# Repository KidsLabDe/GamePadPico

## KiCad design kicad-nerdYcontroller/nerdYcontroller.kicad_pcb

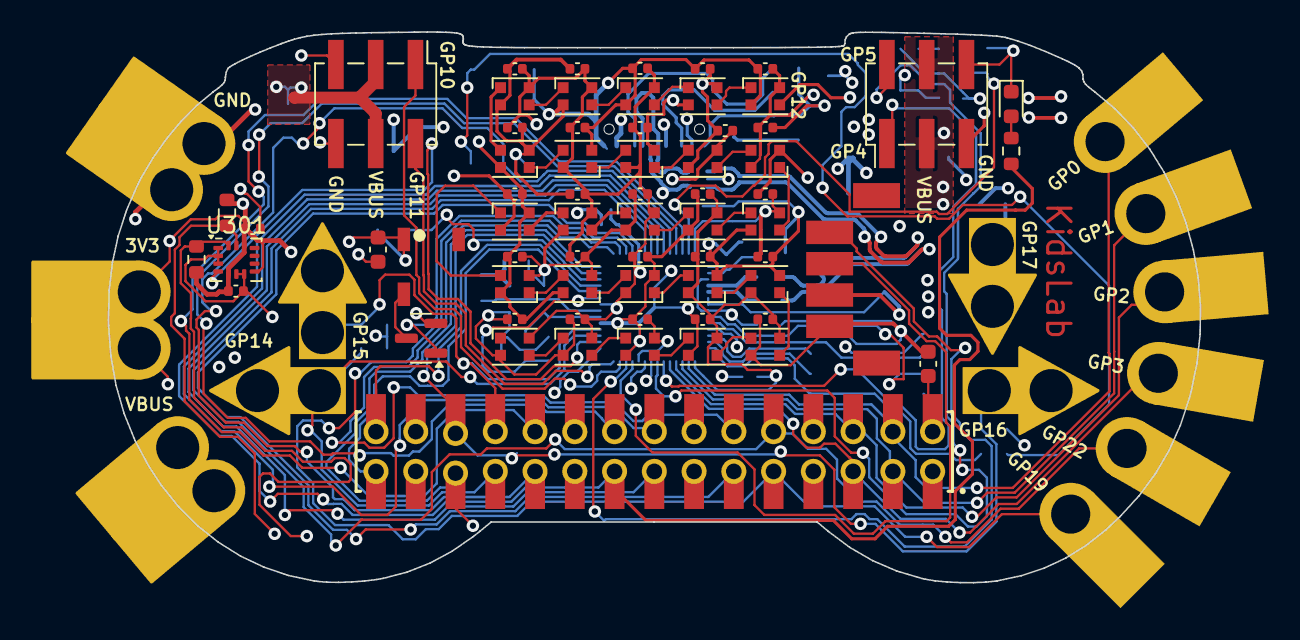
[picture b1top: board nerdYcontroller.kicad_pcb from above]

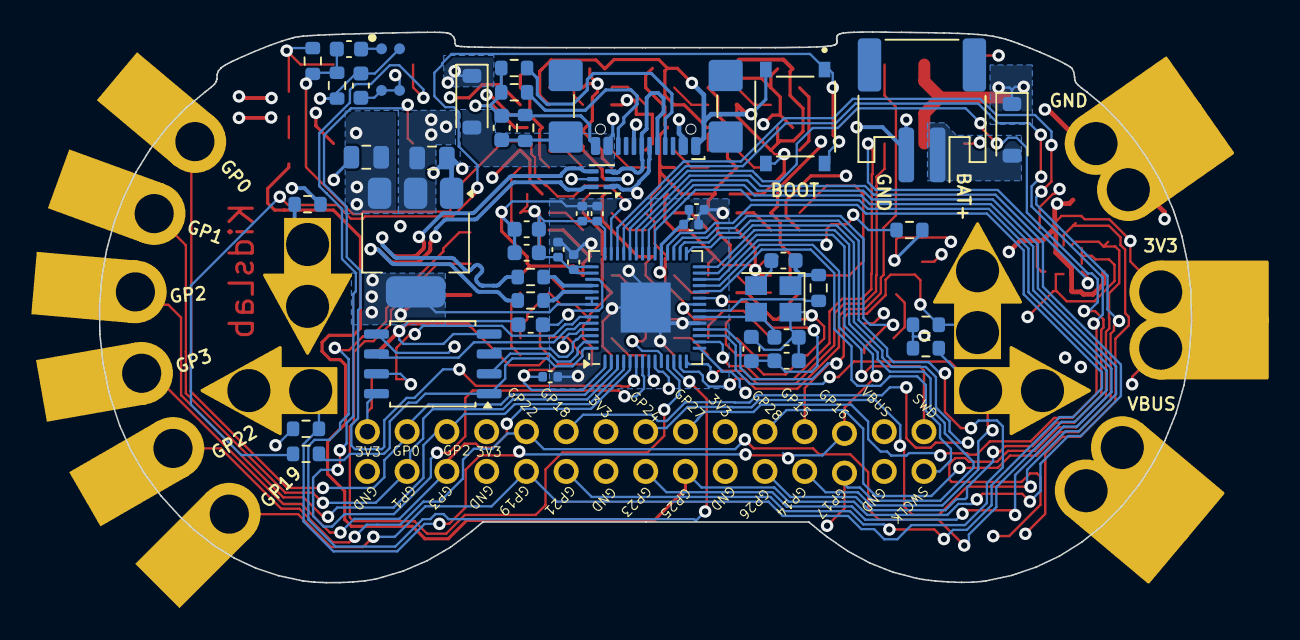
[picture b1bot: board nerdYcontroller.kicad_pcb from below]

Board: 4 copper layers, 69.8 x 35.2 mm, 123 parts (44 on the bottom side), 85 nets.

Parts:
3V3: kroko_doubleedge; DoubleEdge
A301, A302, A303, A304: arrow; Kroko_Arrow
BZ301: Buzzer-FUET-5020; FUET-5020
C101, C113, C114, C304: 100nF; C_0603_1608Metric
C102, C103: 22pF; C_0603_1608Metric
C104, C105, C106, C107, C108, C109, C110, C301, C302, C401, C402, C403, C404, C405, C406, C407, C408, C409, C410, C411, C412, C413, C414, C415, C416, C417, C418, C419, C420, C421, C422, C423, C424, C425: 100nF; C_0402_1005Metric
C111: 10uF; C_0603_1608Metric
C112, C115, C303, C305: 1uF; C_0603_1608Metric
C201, C202: 10uF; C_0805_2012Metric
C203: 1nF; C_0603_1608Metric
D201, D203: B5817W; D_SOD-123
D202: PRTR5V0U2F; WSON-6_1.5x1.5mm_P0.5mm
D301: KT-0603R; LED_0603_1608Metric
D401, D402, D403, D404, D405, D406, D407, D408, D409, D410, D411, D412, D413, D414, D415, D416, D417, D418, D419, D420, D421, D422, D423, D424, D425: WS2812B-2020; LED_WS2812B-2020_PLCC4_2.0x2.0mm
GND301: kroko_doubleedge; DoubleEdge
GP0, GP1, GP2, GP3, GP19, GP22: kroko_edge; Edgeconnector
J201: S2B-PH-SM4-TB; JST_PH_S2B-PH-SM4-TB_1x02-1MP_P2.00mm_Horizontal
J301, J302: Conn_02x03_Odd_Even; PinHeader_2x03_P2.54mm_Vertical_SMD
J303: ZX-HY2.0-4PLT
J304: HLE-115-02-F-DV; SAMTEC_HLE-115-02-F-DV
P201: USB_C_Plug_USB2.0; USB_C_Receptacle_GCT_USB4110
Q301: DDTC113ZCA; SOT-23
R101, R102, R105, R307: 1k; R_0603_1608Metric
R103, R104: 27R; R_0603_1608Metric
R201, R202: 5k1; R_0603_1608Metric
R203: 100; R_0603_1608Metric
R301, R302: 10k; R_0603_1608Metric
R303, R304, R305, R306: 1M; R_0603_1608Metric
R308: 33k; R_0603_1608Metric
R309: 330R; R_0603_1608Metric
S101: TS-1187A-B-A-B; SW_TS-1187A-B-A-B
U101: RP2040; QFN-56-1EP_7x7mm_P0.4mm_EP3.2x3.2mm
U102: W25Q128JVS; SOIC-8_5.23x5.23mm_P1.27mm
U201: AMS1117-3.3; SOT-223-3_TabPin2
U301: LSM6DS3TR-C; LGA-14_3x2.5mm_P0.5mm_LayoutBorder3x4y
U302: LMA3722T421-OA5
VBUS301: kroko_doubleedge; DoubleEdge
Y101: Crystal_GND24; Crystal_SMD_3225-4Pin_3.2x2.5mm
outline: Gamecontroller Outline

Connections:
+1V1: C113.1, C114.1, C115.1, U101.23 (DVDD), U101.45 (VREG_VOUT), U101.50 (DVDD)
+3V3: 3V3.1, BZ301.1 (+), C101.1, C104.2, C105.2, C106.2, C107.2, C108.2, C109.2, C110.2, C111.1, C112.1, C202.1, C301.2, C302.2, C304.1, C305.1, C401.1, C402.1, C403.1, C404.1, C405.1, C406.1, C407.1, C408.1, C409.1, C410.1, C411.1, C412.1, C413.1, C414.1, C415.1, C416.1, C417.1, C418.1, C419.1, C420.1, C421.1, C422.1, C423.1, C424.1, C425.1, D401.4 (VDD), D402.4 (VDD), D403.4 (VDD), D404.4 (VDD), D405.4 (VDD), D406.4 (VDD), D407.4 (VDD), D408.4 (VDD), D409.4 (VDD), D410.4 (VDD), D411.4 (VDD), D412.4 (VDD), D413.4 (VDD), D414.4 (VDD), D415.4 (VDD), D416.4 (VDD), D417.4 (VDD), D418.4 (VDD), D419.4 (VDD), D420.4 (VDD), D421.4 (VDD), D422.4 (VDD), D423.4 (VDD), D424.4 (VDD), D425.4 (VDD), J303.3, J304.02, J304.08, J304.14, J304.20, R102.2, R301.1, R302.1, R308.1, U101.1 (IOVDD), U101.10 (IOVDD), U101.22 (IOVDD), U101.33 (IOVDD), U101.42 (IOVDD), U101.43 (ADC_AVDD), U101.44 (VREG_IN), U101.48 (USB_VDD), U101.49 (IOVDD), U102.8 (VCC), U201.2 (VO), U301.5 (VDDIO), U301.8 (VDD), U301.12 (CS), U302.2 (VDD)
/FLASH_CS: R101.2, U101.56 (QSPI_SS), U102.1 (~CS)
/FLASH_SCLK: U101.52 (QSPI_SCLK), U102.6 (CLK)
/FLASH_SD0: U101.53 (QSPI_SD0), U102.5 (DI(IO0))
/FLASH_SD1: U101.55 (QSPI_SD1), U102.2 (DO(IO1))
/FLASH_SD2: U101.54 (QSPI_SD2), U102.3 (IO2)
/FLASH_SD3: U101.51 (QSPI_SD3), U102.7 (IO3)
/N_USBBOOT: R101.1, S101.A, S101.B
/Peripherals/GP0: GP0.1, J304.04, U101.2 (GPIO0)
/Peripherals/GP1: GP1.1, J304.03, U101.3 (GPIO1)
/Peripherals/GP2: GP2.1, J304.06, U101.4 (GPIO2)
/Peripherals/GP3: GP3.1, J304.05, U101.5 (GPIO3)
/Peripherals/GP4/SERVO_2: J302.1, U101.6 (GPIO4)
/Peripherals/GP5/SERVO_3: J302.2, U101.7 (GPIO5)
/Peripherals/GP6/IMU_SDA: R301.2, U101.8 (GPIO6), U301.14 (SDA)
/Peripherals/GP7/IMU_SCL: R302.2, U101.9 (GPIO7), U301.13 (SCL)
/Peripherals/GP8/Grove_D1: J303.2, U101.11 (GPIO8)
/Peripherals/GP9/Grove_D0: J303.1, U101.12 (GPIO9)
/Peripherals/GP10/SERVO_0: J301.1, U101.13 (GPIO10)
/Peripherals/GP11/SERVO_1: J301.2, U101.14 (GPIO11)
/Peripherals/GP12/NEOPIXEL: D401.3 (DIN), U101.15 (GPIO12)
/Peripherals/GP13/INTR: U101.16 (GPIO13), U301.4 (INT1)
/Peripherals/GP14/ArrowLeft: A301.1, J304.23, R303.1, U101.17 (GPIO14)
/Peripherals/GP15/ArrowUp: A302.1, J304.24, R304.1, U101.18 (GPIO15)
/Peripherals/GP16/ArrowRight: A303.1, J304.26, R305.1, U101.27 (GPIO16)
/Peripherals/GP17/ArrowDown: A304.1, J304.25, R306.1, U101.28 (GPIO17)
/Peripherals/GP18: J304.12, U101.29 (GPIO18)
/Peripherals/GP19: GP19.1, J304.09, U101.30 (GPIO19)
/Peripherals/GP20/Buzzer: Q301.1 (B), U101.31 (GPIO20)
/Peripherals/GP21: J304.11, U101.32 (GPIO21)
/Peripherals/GP22: GP22.1, J304.10, U101.34 (GPIO22)
/Peripherals/GP23: J304.15, U101.35 (GPIO23)
/Peripherals/GP24: J304.16, U101.36 (GPIO24)
/Peripherals/GP25/LED: J304.17, R309.1, U101.37 (GPIO25)
/Peripherals/GP26: J304.21, U101.38 (GPIO26_ADC0)
/Peripherals/GP27: J304.18, U101.39 (GPIO27_ADC1)
/Peripherals/GP28: J304.22, U101.40 (GPIO28_ADC2)
/Peripherals/GP29/MIC_OUT: C303.2, R307.1, R308.2, U101.41 (GPIO29_ADC3)
/SWCLK: J304.29, U101.24 (SWCLK)
/SWD: J304.30, U101.25 (SWD)
/VBUS: C201.1, D201.1 (K), D203.1 (K), J301.3, J301.4, J302.3, J302.4, J304.28, U201.3 (VI), VBUS301.1
/d+: R103.2, U101.47 (USB_DP)
/d-: R104.2, U101.46 (USB_DM)
/power-and-usb/USBC-D+: D202.1 (IO1), P201.A6 (D+), P201.B6 (D+)
/power-and-usb/USBC-D-: D202.3 (IO2), P201.A7 (D-), P201.B7 (D-)
/power-and-usb/usb_vcc: D201.2 (A), D202.5 (VCC), P201.A4 (VBUS), P201.A9 (VBUS), P201.B4 (VBUS), P201.B9 (VBUS)
/usb_d+: D202.6 (IO1), R103.1
/usb_d-: D202.4 (IO2), R104.1
GND: C101.2, C102.2, C103.2, C104.1, C105.1, C106.1, C107.1, C108.1, C109.1, C110.1, C111.2, C112.2, C113.2, C114.2, C115.2, C201.2, C202.2, C203.2, C301.1, C302.1, C304.2, C305.2, C401.2, C402.2, C403.2, C404.2, C405.2, C406.2, C407.2, C408.2, C409.2, C410.2, C411.2, C412.2, C413.2, C414.2, C415.2, C416.2, C417.2, C418.2, C419.2, C420.2, C421.2, C422.2, C423.2, C424.2, C425.2, D202.2 (GND), D301.1 (K), D401.2 (VSS), D402.2 (VSS), D403.2 (VSS), D404.2 (VSS), D405.2 (VSS), D406.2 (VSS), D407.2 (VSS), D408.2 (VSS), D409.2 (VSS), D410.2 (VSS), D411.2 (VSS), D412.2 (VSS), D413.2 (VSS), D414.2 (VSS), D415.2 (VSS), D416.2 (VSS), D417.2 (VSS), D418.2 (VSS), D419.2 (VSS), D420.2 (VSS), D421.2 (VSS), D422.2 (VSS), D423.2 (VSS), D424.2 (VSS), D425.2 (VSS), GND301.1, J201.2, J301.5, J301.6, J302.5, J302.6, J303.4, J304.01, J304.07, J304.13, J304.19, J304.27, P201.A1 (GND), P201.A12 (GND), P201.B1 (GND), P201.B12 (GND), Q301.2 (E), R201.1, R202.1, R203.1, R303.2, R304.2, R305.2, R306.2, R307.2, S101.C, S101.D, U101.19 (TESTEN), U101.57 (GND), U102.4 (GND), U201.1 (GND), U301.1 (SDO/SA0), U301.2 (SDX), U301.3 (SCX), U301.6 (GND), U301.7 (GND), U302.3 (GND), U302.4 (GND), Y101.2, Y101.4
unnamed: BZ301.2 (-), Q301.3 (C)
unnamed: C102.1, R105.2, Y101.1
unnamed: D203.2 (A), J201.1
unnamed: D301.2 (A), R309.2
unnamed: D401.1 (DOUT), D403.3 (DIN)
unnamed: D402.3 (DIN), D409.1 (DOUT)
unnamed: D402.1 (DOUT), D404.3 (DIN)
unnamed: D403.1 (DOUT), D405.3 (DIN)
unnamed: D404.1 (DOUT), D406.3 (DIN)
unnamed: D405.1 (DOUT), D407.3 (DIN)
unnamed: D406.1 (DOUT), D408.3 (DIN)
unnamed: D407.1 (DOUT), D409.3 (DIN)
unnamed: D408.1 (DOUT), D410.3 (DIN)
unnamed: D410.1 (DOUT), D411.3 (DIN)
unnamed: D411.1 (DOUT), D412.3 (DIN)
unnamed: D412.1 (DOUT), D413.3 (DIN)
unnamed: D413.1 (DOUT), D414.3 (DIN)
unnamed: D414.1 (DOUT), D415.3 (DIN)
unnamed: D415.1 (DOUT), D416.3 (DIN)
unnamed: D416.1 (DOUT), D417.3 (DIN)
unnamed: D417.1 (DOUT), D418.3 (DIN)
unnamed: D418.1 (DOUT), D419.3 (DIN)
unnamed: D419.1 (DOUT), D420.3 (DIN)
unnamed: D420.1 (DOUT), D421.3 (DIN)
unnamed: D421.1 (DOUT), D422.3 (DIN)
unnamed: D422.1 (DOUT), D423.3 (DIN)
unnamed: D423.1 (DOUT), D424.3 (DIN)
unnamed: D424.1 (DOUT), D425.3 (DIN)
unnamed: P201.A5 (CC), R201.2
unnamed: C203.1, P201.S1 (SHIELD), R203.2
unnamed: P201.B5 (VCONN), R202.2
unnamed: R102.1, U101.26 (RUN)
unnamed: C103.1, U101.20 (XIN), Y101.3
unnamed: R105.1, U101.21 (XOUT)
unnamed: C303.1, U302.1 (out)

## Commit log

2025-03-30 svg dateien der platine
2025-05-15 Firmware für die neue platine
2025-05-16 fixing missing usb-c 2-way connectivity
2025-07-16 Uf2 datei war zu groß - neues CP
